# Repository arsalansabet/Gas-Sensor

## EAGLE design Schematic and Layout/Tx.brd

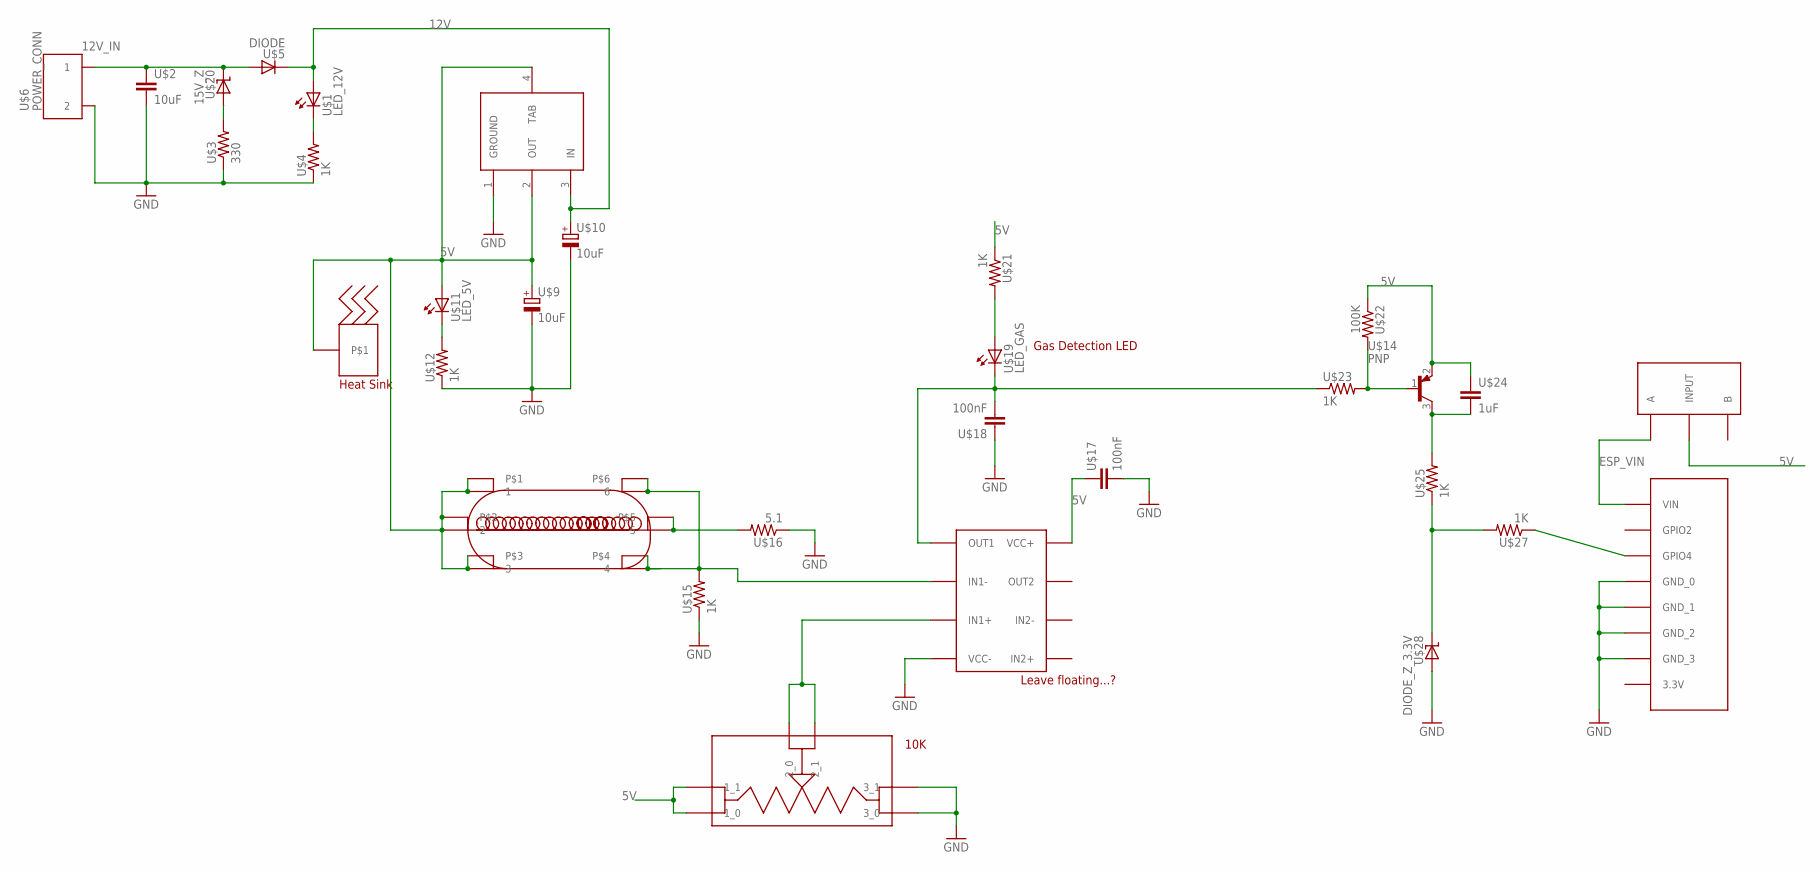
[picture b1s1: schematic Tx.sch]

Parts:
U$1: LED_12V; LED_1206
U$2: 10uF; C1206
U$3: 330; R1206
U$4, U$12, U$15, U$21, U$23, U$25, U$27: 1K; R1206
U$5: DIODE; DIDOE_1206
U$6: POWER_CONN; PC_1935161
U$7: LM393; SO8
U$8: 5V_REG; SOT223
U$9, U$10: 10uF; 153CLV-0405
U$11: LED_5V; LED_1206
U$13: MQ; MQ_GAS
U$14: PNP; SOT23
U$16: 5.1; R1206
U$17, U$18: 100nF; C1206
U$19: LED_GAS; LED_1206
U$20: 15V_Z; Z_1005
U$22: 100K; R1206
U$24: 1uF; C1206
U$28: DIODE_Z_3.3V; SOD-323
U$29: ESP8266; ESP
U$30: POTENTIOMETER
U$31: HEAT_SINK; THERMAL
U$32: SPDT

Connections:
5V: U$7.8 (VCC+), U$8.2 (OUT), U$8.4 (TAB), U$9.+, U$11.1 (HI), U$13.1, U$13.2, U$13.3, U$13.7, U$13.8, U$13.9, U$14.2 (E), U$17.1, U$21.1, U$22.1, U$24.1, U$30.1_0, U$30.1_1, U$31.P$1, U$32.IN (INPUT)
12V: U$1.1 (HI), U$5.2 (LO), U$8.3 (IN), U$10.+
12V_IN: U$2.1, U$5.1 (HI), U$6.1, U$20.2 (LO)
ESP_VIN: U$29.VIN, U$32.A
GND: U$2.2, U$3.1, U$4.1, U$6.2, U$7.4 (VCC-), U$8.1 (GROUND), U$9.-, U$10.-, U$12.1, U$15.1, U$16.1, U$17.2, U$18.1, U$28.P$1 (HI), U$29.GND_0, U$29.GND_1, U$29.GND_2, U$29.GND_3, U$30.3_0, U$30.3_1
unnamed: U$1.2 (LO), U$4.2
unnamed: U$11.2 (LO), U$12.2
unnamed: U$13.5, U$13.11, U$16.2
unnamed: U$3.2, U$20.1 (HI)
unnamed: U$7.3 (IN1+), U$30.2_0, U$30.2_1
unnamed: U$7.1 (OUT1), U$18.2, U$19.2 (LO), U$23.1
unnamed: U$14.1 (B), U$22.2, U$23.2
unnamed: U$19.1 (HI), U$21.2
unnamed: U$14.3 (C), U$24.2, U$25.2
unnamed: U$25.1, U$27.2, U$28.P$2 (LO)
unnamed: U$27.1, U$29.GPIO4
unnamed: U$7.2 (IN1-), U$13.4, U$13.6, U$13.10, U$13.12, U$15.2

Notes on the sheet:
Leave floating...?
Gas Detection LED
10K

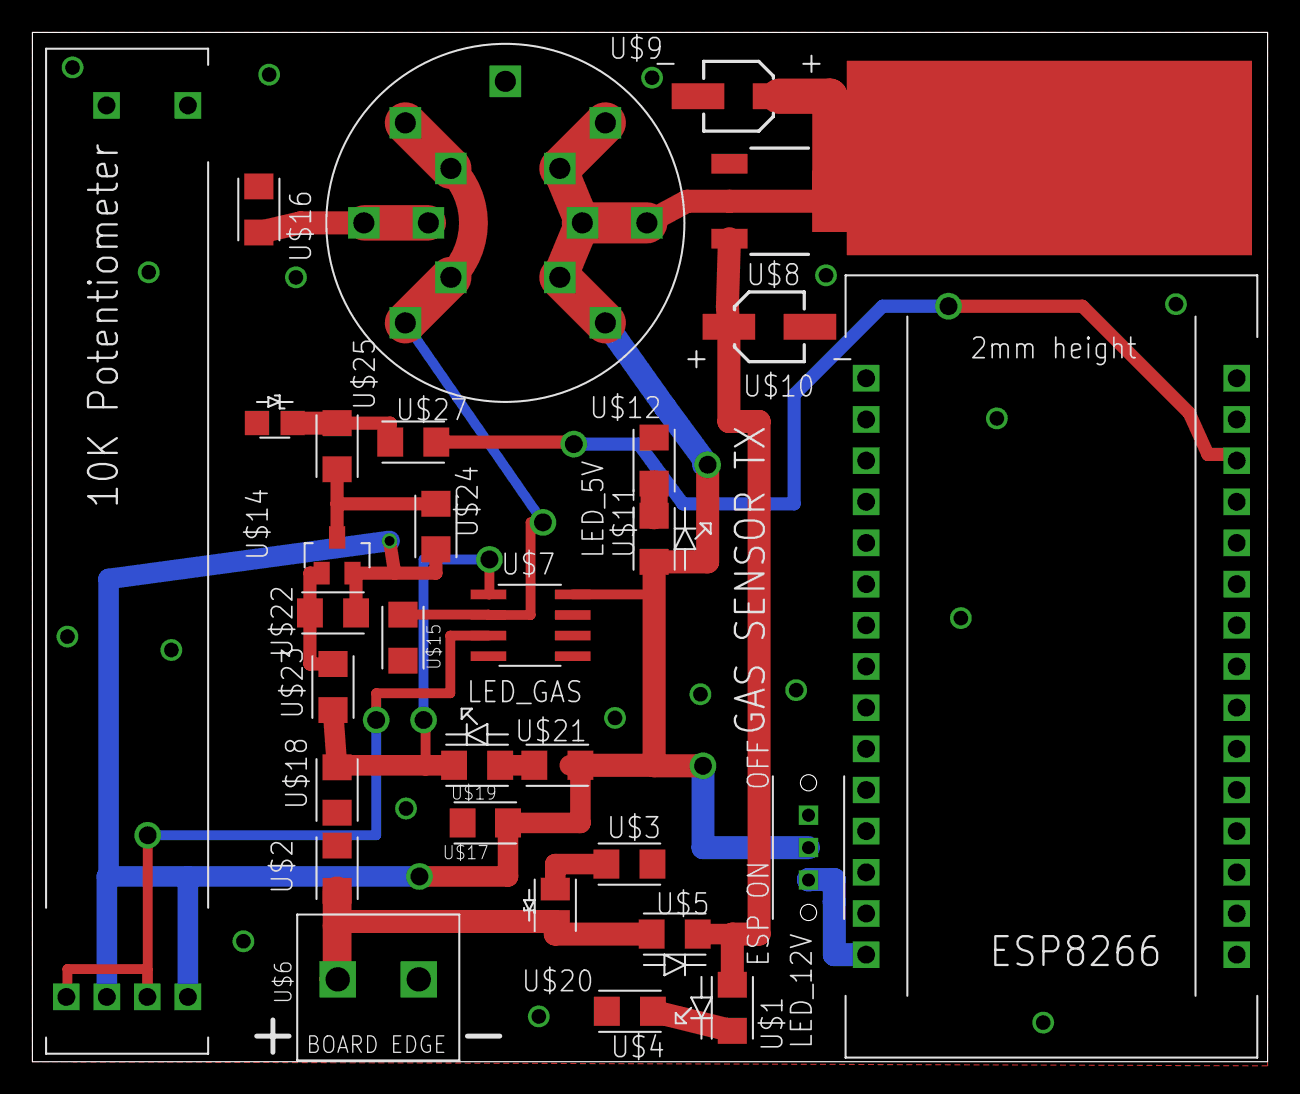
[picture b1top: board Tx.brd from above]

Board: 2 copper layers, 76.2 x 63.5 mm, 31 parts (0 on the bottom side), 17 nets.

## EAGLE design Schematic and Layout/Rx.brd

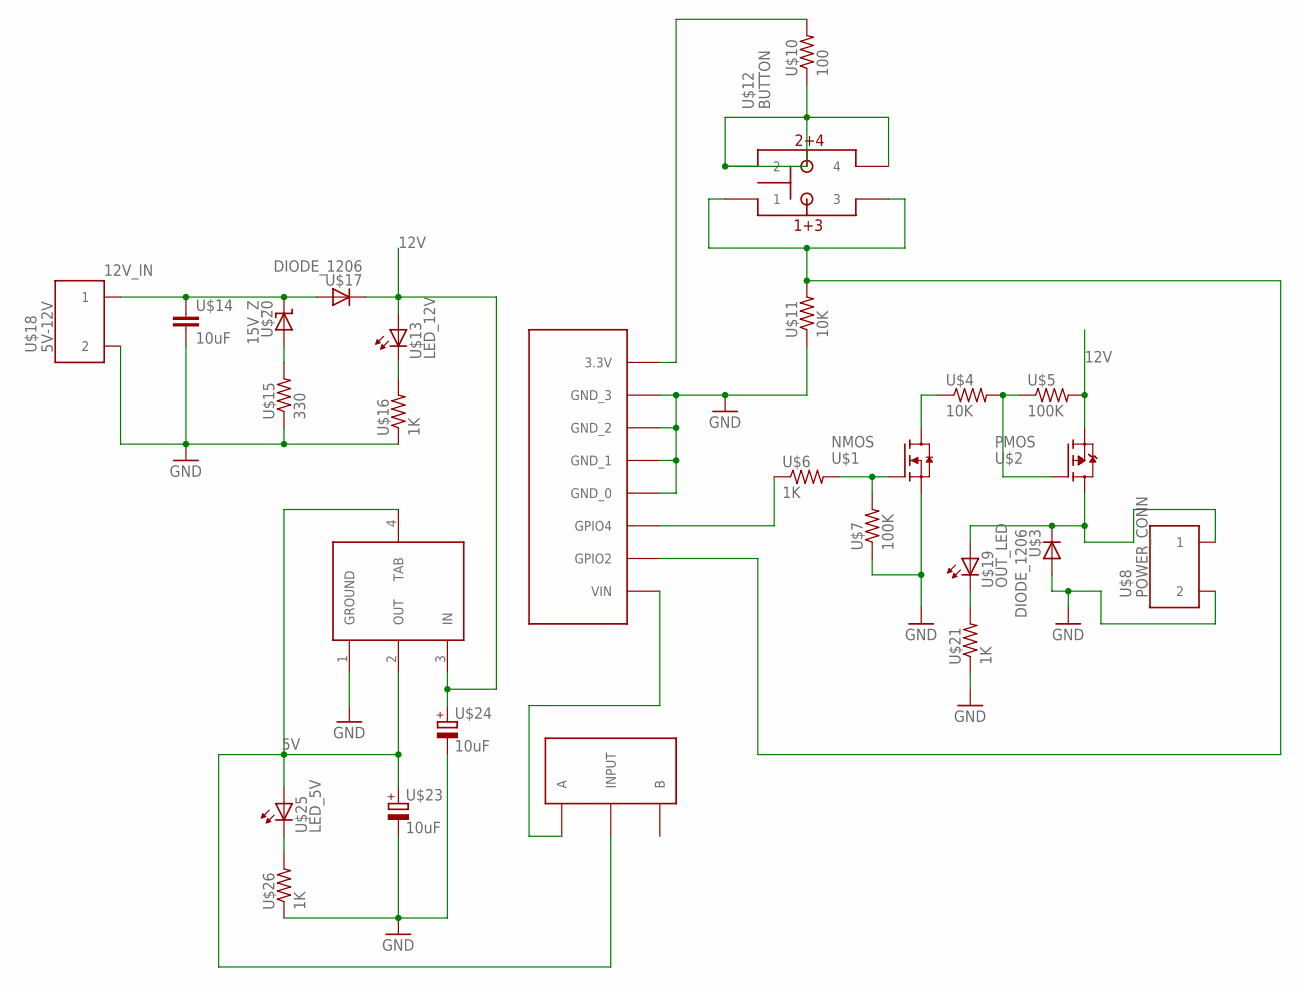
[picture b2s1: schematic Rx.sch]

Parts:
U$1: NMOS; SOT23
U$2: PMOS; D-PAK_TO252AA
U$3, U$17: DIODE_1206; DIDOE_1206
U$4, U$11: 10K; R1206
U$5, U$7: 100K; R1206
U$6, U$16, U$21, U$26: 1K; R1206
U$8: POWER_CONN; PC_1935161
U$9: ESP8266; ESP
U$10: 100; R1206
U$12: BUTTON
U$13: LED_12V; LED_1206
U$14: 10uF; C1206
U$15: 330; R1206
U$18: 5V-12V; PC_1935161
U$19: OUT_LED; LED_1206
U$20: 15V_Z; Z_1005
U$22: 5V_REG; SOT223
U$23, U$24: 10uF; 153CLV-0405
U$25: LED_5V; LED_1206
U$27: SPDT

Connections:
5V: U$22.2 (OUT), U$22.4 (TAB), U$23.+, U$25.1 (HI), U$27.IN (INPUT)
12V: U$2.3 (S), U$5.2, U$13.1 (HI), U$17.2 (LO), U$22.3 (IN), U$24.+
12V_IN: U$14.1, U$17.1 (HI), U$18.1, U$20.2 (LO)
GND: U$1.2 (S), U$3.1 (HI), U$7.1, U$8.2, U$9.GND_0, U$9.GND_1, U$9.GND_2, U$9.GND_3, U$11.1, U$14.2, U$15.1, U$16.1, U$18.2, U$21.1, U$22.1 (GROUND), U$23.-, U$24.-, U$26.1
unnamed: U$1.1 (G), U$6.2, U$7.2
unnamed: U$6.1, U$9.GPIO4
unnamed: U$1.3 (D), U$4.1
unnamed: U$2.1 (G), U$4.2, U$5.1
unnamed: U$19.2 (LO), U$21.2
unnamed: U$2.4 (D), U$3.2 (LO), U$8.1, U$19.1 (HI)
unnamed: U$9.GPIO2, U$11.2, U$12.1, U$12.3
unnamed: U$25.2 (LO), U$26.2
unnamed: U$10.1, U$12.2, U$12.4
unnamed: U$9.3.3_1 (3.3V), U$10.2
unnamed: U$13.2 (LO), U$16.2
unnamed: U$15.2, U$20.1 (HI)
unnamed: U$9.VIN, U$27.A

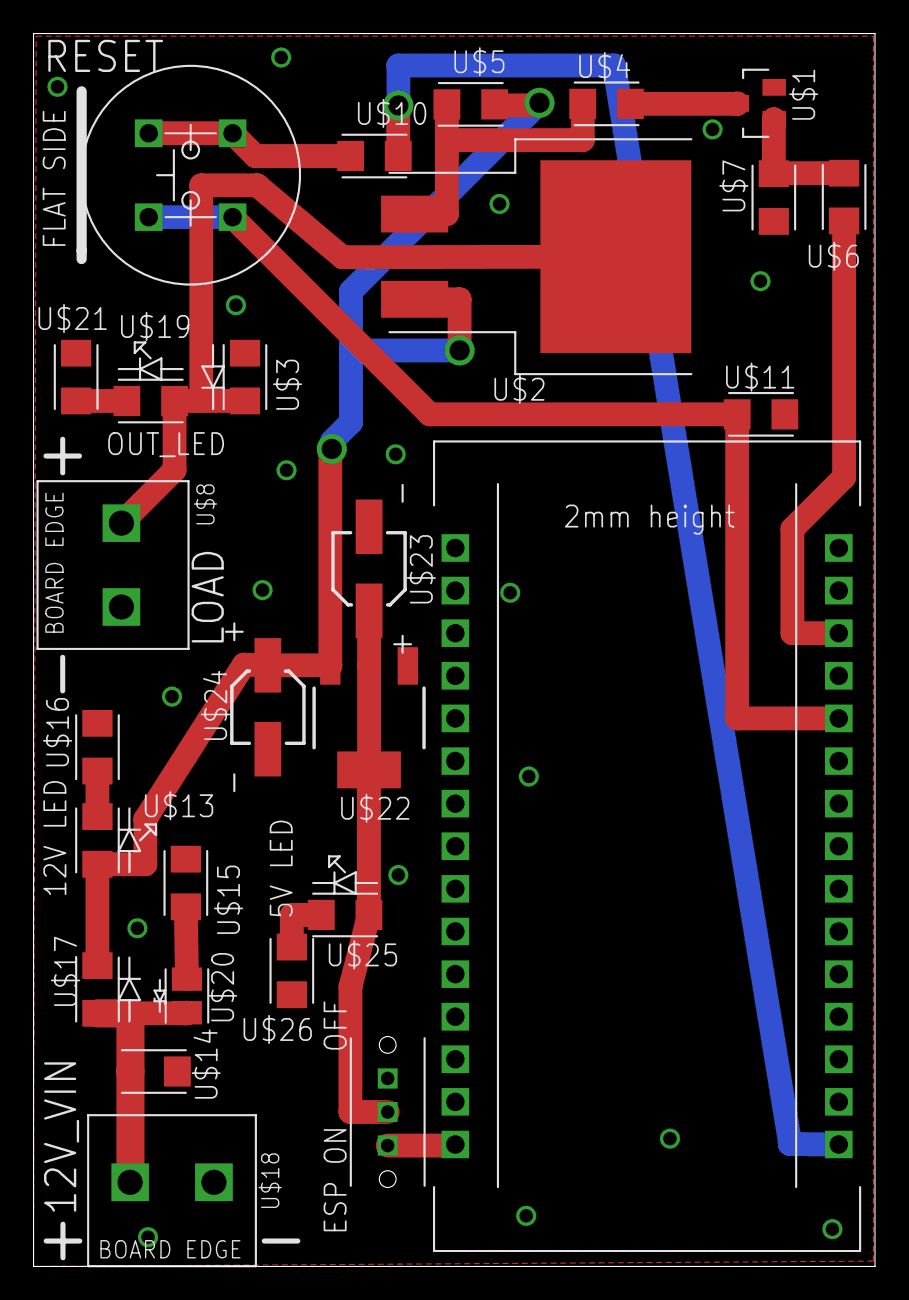
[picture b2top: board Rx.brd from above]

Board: 2 copper layers, 50.2 x 73.5 mm, 27 parts (0 on the bottom side), 17 nets.

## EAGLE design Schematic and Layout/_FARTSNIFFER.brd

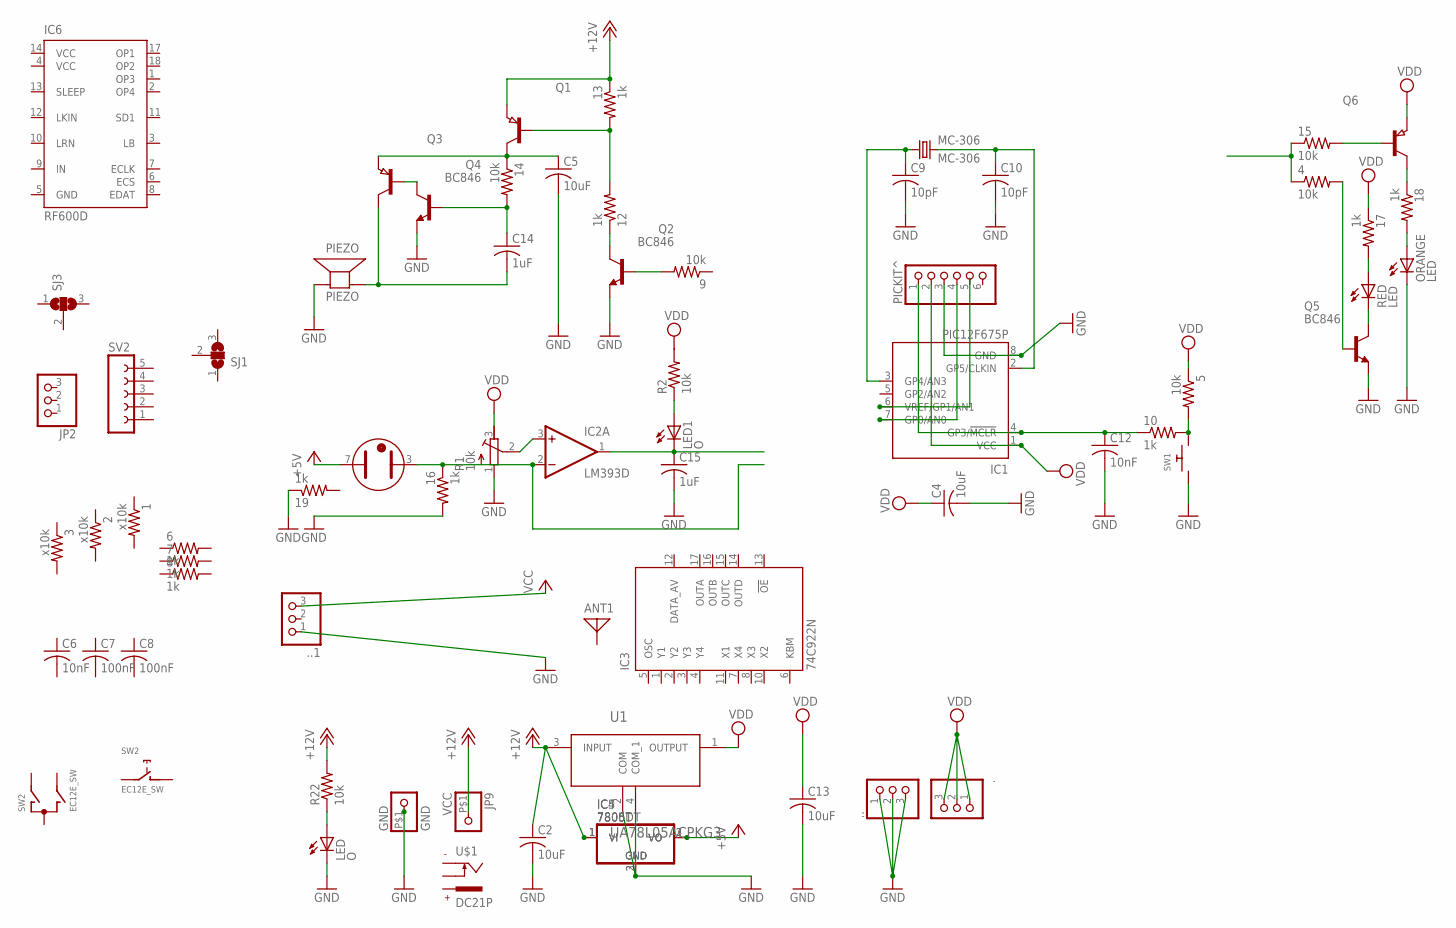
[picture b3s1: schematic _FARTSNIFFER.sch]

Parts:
1, 2, 3: x10k; R1206
4, 5, 9, 14, 15: 10k; R1206
6, 7, 8, 10, 12, 13, 16, 17, 18, 19: 1k; R1206
., .., ..1: PINHD-1X3CB; 1X03-CLEANBIG
ANT1: ANTENNA; PAD-01
C2, C4, C5, C13: 10uF; C1210
C6, C12: 10nF; C1210
C7, C8: 100nF; C1210
C9, C10: 10pF; C1210
C14, C15: 1uF; C1210
GND: GND; 1X1-BIGPOGO
IC1: PIC12F675P; DIL8
IC2: LM393D; SO08
IC3: 74C922N; DIL18
IC4: 7806DT; TO252
IC5: 7805T; TO220H
IC6: RF600D; DIL18
JP2: PINHD-1X3CB; 1X03-CLEANBIG
JP9: VCC; 1X1-BIGPOGO
LED, LED1: O; CHIPLED_1206
MC-306: MC-306; MPN MC-306 60.0KHZ 100PPM ,12.5PF
ORANGE: LED; LED5MM
PICKIT^: PINHD-1X6LOCK; 1X06-BIGLOCK
PIEZO: PIEZO; AL60P
Q1, Q3: PNP-TRANSISTOR_SOT89; SOT89
Q2, Q4, Q5: BC846; SOT23
Q6: PNP-TRANSISTOR_SOT23; SOT23
R1: 10k; RTRIM64W
R2, R22: 10k; R1206
RED: LED; LED5MM
SJ1, SJ3: SJ2W; SJ_2
ST1: STABI; MINI_P
SV2: FE05-1
SW1: SWITCH_PUSHBUTTONEVQ-PE; TACT_PANA-EVQ
SW2: EC12E_SW; ALPS_EC12E_SW
U1: UA78L05ACPKG3; SOT150P400X160-4N
U$1: DC21P; DCSKTP

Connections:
+5V: IC4.2 (VO), IC5.3 (VO)
+12V: 13.1, C2.1, IC4.1 (VI), IC5.1 (VI), JP9.P$1, Q1.3 (E), R22.2, U1.3 (INPUT)
GND: 16.2, 19.1, ...1, ...2, ...3, ..1.1, C2.2, C4.2, C5.2, C9.2, C10.2, C12.2, C13.2, C15.2, GND.P$1, IC1.8 (GND), IC3.9 (GND), IC4.3 (GND), IC5.2 (GND), IC6.5 (GND), LED.C, ORANGE.K (C), PICKIT^.3, PIEZO.2 (-), Q2.2 (E), Q4.2 (E), Q5.2 (E), R1.1 (A), SW1.P$1, U1.2 (COM), U1.4 (COM_1)
unnamed: 9.2, Q2.1 (B)
unnamed: 5.2, 10.2, SW1.P$2
unnamed: 10.1, C12.1, IC1.4 (GP3/!MCLR), PICKIT^.1
unnamed: IC1.7 (GP0/AN0), PICKIT^.4
unnamed: Q5.3 (C), RED.K (C)
unnamed: 12.1, Q2.3 (C)
unnamed: 12.2, 13.2, Q1.1 (B)
unnamed: 4.2, Q5.1 (B)
unnamed: 18.1, Q6.3 (C)
unnamed: 15.2, Q6.1 (B)
unnamed: 4.1, 15.1
unnamed: 16.1, IC2.2 (-IN), ST1.3 (A)
unnamed: IC2.3 (+IN), R1.2 (S)
unnamed: LED1.A, R2.1
unnamed: Q3.1 (B), Q4.3 (C)
unnamed: 14.1, C5.1, Q1.2 (C), Q3.3 (E)
unnamed: 14.2, C14.1, Q4.1 (B)
unnamed: C15.1, IC2.1 (OUT), LED1.C
unnamed: 18.2, ORANGE.A
unnamed: 17.2, RED.A
unnamed: C9.1, IC1.3 (GP4/AN3), MC-306.1
unnamed: C10.1, IC1.2 (GP5/CLKIN), MC-306.4 (2)
unnamed: LED.A, R22.1
V+: IC2.8 (V+)
V-: IC2.4 (V-)
VCC: ..1.3, IC3.18 (VCC), IC6.14 (VCC)
VDD: 5.1, 17.1, ..1, ..2, ..3, C4.1, C13.1, IC1.1 (VCC), PICKIT^.2, Q6.2 (E), R1.3 (E), R2.2, ST1.7 (K), U1.1 (OUTPUT)
VS: C14.2, PIEZO.1 (+), Q3.2 (C)

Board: 2 copper layers, 67 parts (16 on the bottom side), 29 nets, no tracks yet.

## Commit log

2017-01-13 Adding folders.
    Test file is so that github would create the folder. Will delete later
    when we have stuff.
2017-01-13 rudimentary project design
2017-01-13 initial testing
2017-01-13 encoder/decoder
2017-01-13 catalytic gas sensor
2017-01-13 microcontroller
2017-01-13 laws and regulations
2017-01-13 various parts
2017-01-31 Very Nice Presentation
    I added a couple of pictures and expanded the frequency range.
    Kam
2017-02-16 Added useful links for us
2017-02-26 Added more useful links
2017-03-02 Added ISP programming link
2017-03-17 Create .gitkeep
    test
2017-03-17 Added initial documentation
    Documentation on how to talk to our microcontrollers
2017-03-17 Updated links and leads
    Might be some additions since I last updated
2017-03-17 Create .txt
    created folder
2017-03-17 Added my initial code for connecting to my hotspot
    Copied code, changed baud rate, ssid, password, and added debugging messages.
    Doesn't work yet, need to fix schematic or try arduino nano
2017-03-19 Uploading Project Schedule
2017-03-19 Added Schedule and PDS/requirements from Google Drive
2017-03-19 Added Arsalan's debugging steps to Transceiver doc
2017-03-23 Updated Project Schedule
2017-04-14 softAP guide updated
    Added trouble shooting guide and added serial pinout
2017-04-16 NodeMCU 1.0 setup walk-through
    Set up my ESP modules with these steps, I was then able to connect two wifi Modules together using the code referenced in https://github.com/arsalansabet/Gas-Sensor/tree/master/Code/Test%20Code
2017-04-16 Useful features and functions
2017-04-17 Added boards manager
    Showed how to add the ESP boards to the arduino IDE
2017-04-18 Added TCP info
2017-04-18 Updated notes
    No softAP WPS feature found. Doesn't look possible to use WPS at this point
    We should use station mode instead of client mode
2017-04-20 Added missing steps
    Made more clear, distinguished between library and board setup
2017-04-21 Use this instead of WifiClient
    WifiStation will reconnect if the network goes down
2017-04-26 Will blink an LED on GPIO2
2017-04-26 Create README!!!!
2017-04-26 These will talk to each other
2017-04-26 Read and print the status of input GPIO2
2017-04-26 Connect with your laptop and toggle GPIO2 high and low
2017-04-26 Connect with your laptop and toggle GPIO4 high and low
    This prevents output high during boot! This GPIO must be tied low
2017-04-28 WifiAccessPoint is also a webserver
2017-04-29 These will connect and the client will turn on the LED of GPIO4 on the server
2017-04-29 Used GPIO4 on both client and server. If GPIO 4 on client goes high than sensor should be tripped on server at GPIO4.
    Used GPIO4 on both client and server. If GPIO4 on client goes high than
    sensor should be tripped on server at GPIO4.
2017-04-29 Code modified so on start up the sensor won't trip.
2017-04-29 Function code with clear function
2017-04-30 With Clear function
2017-04-30 Clear function and timeout function
2017-05-11 Final BOM
2017-05-11 Add files via upload
    I added an output LED on the receiver side and put some silkscreen on the bottom with our first names.
    I also added "RESET" next to the button on the silkscreen for the rx.
    Input capacitance decreased to 10uF. Too expensive to get 470uF.
2017-05-11 Fixed major error on tx board. Cap overlapped connector
2017-05-11 Fixed major error on Tx. Comp overlapped connector
2017-05-11 Minor changes
2017-05-11 Major error fixed, was missing 5V on PNP
2017-05-11 Added stapled grounds
2017-05-11 Added LED indicator silkscreen
2017-05-12 Added comments to our code
2017-05-12 Updated project schedule w/ progress for all tasks.
    We are on track!
2017-05-17 Modified comments and added password
2017-05-27 ESPs now run off of 5 V
2017-05-27 Definitively added zener diodes
2017-05-28 Updated comment, sounded like device was connecting to a wifi network
2017-05-31 Fixed TX issue
2017-06-04 Removed old, commented code
